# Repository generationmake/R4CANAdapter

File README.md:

# R4CANAdapter
CAN adapter for the Arduino UNO R4 minima and Arduino UNO R4 WiFi

## PCB
### Top

### Bottom

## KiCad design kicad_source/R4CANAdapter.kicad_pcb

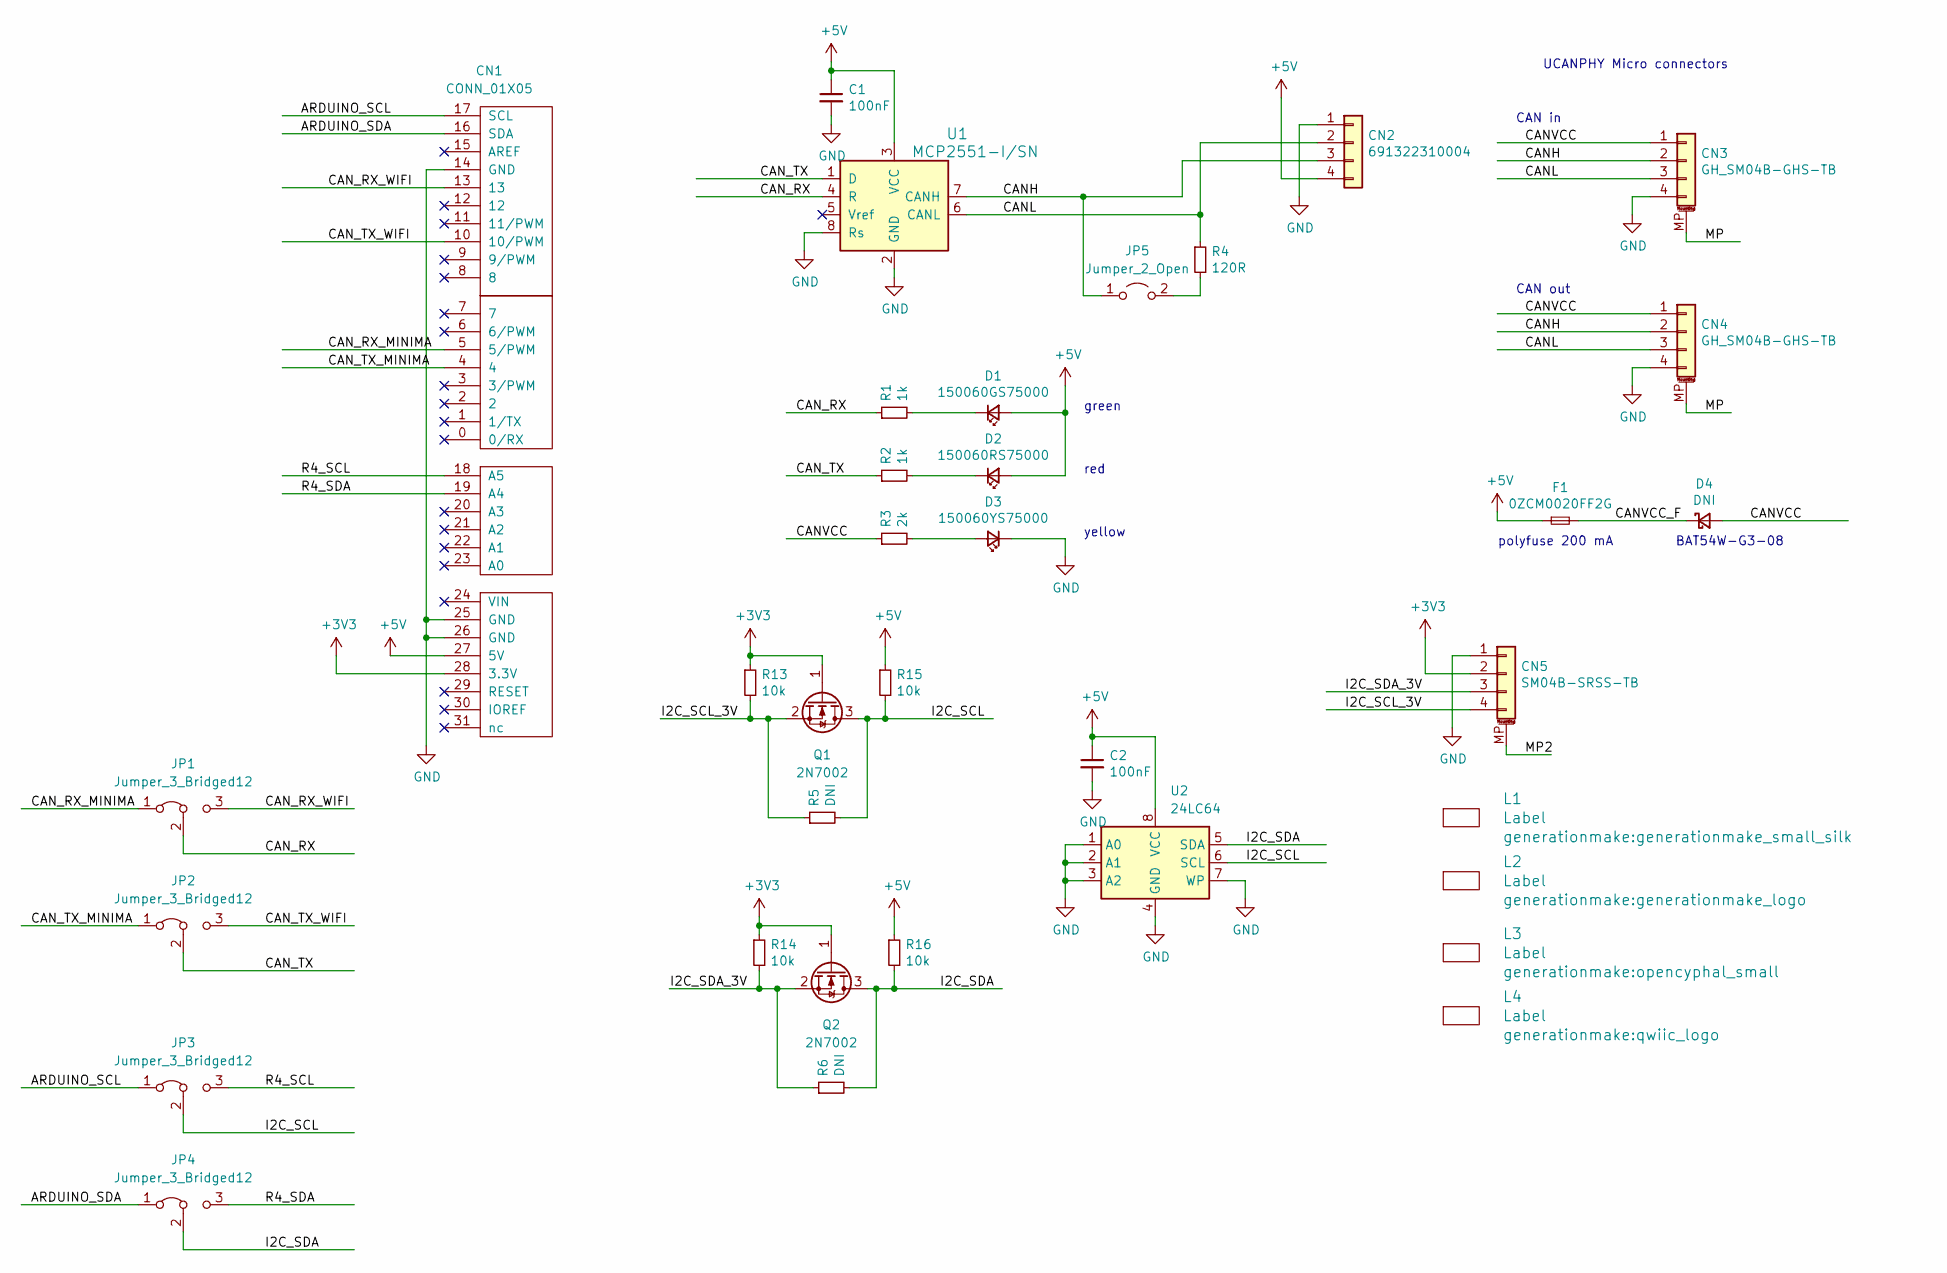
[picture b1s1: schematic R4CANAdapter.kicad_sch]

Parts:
C1, C2: 100nF; C_0603_1608Metric
CN1: CONN_01X05; ARDUINO
CN2: 691322310004; WR-TBL_691322310004
CN3, CN4: GH_SM04B-GHS-TB; JST_GH_SM04B-GHS-TB_1x04-1MP_P1.25mm_Horizontal
CN5: SM04B-SRSS-TB; JST_SH_SM04B-SRSS-TB_1x04-1MP_P1.00mm_Horizontal
D1: 150060GS75000; LED_0603_1608Metric
D2: 150060RS75000; LED_0603_1608Metric
D3: 150060YS75000; LED_0603_1608Metric
D4: DNI; D_SOD-123
F1: 0ZCM0020FF2G; R_0603_1608Metric
JP1, JP2, JP3, JP4: Jumper_3_Bridged12; PinHeader_1x03_P2.54mm_Vertical
JP5: Jumper_2_Open; PinHeader_1x02_P2.54mm_Vertical
L1: Label; generationmake_small_silk
L2: Label; generationmake_logo
L3: Label; opencyphal_small
L4: Label; qwiic_logo
Q1, Q2: 2N7002; SOT-23
R1, R2: 1k; R_0603_1608Metric
R3: 2k; R_0603_1608Metric
R4: 120R; R_0603_1608Metric
R5, R6: DNI; R_0603_1608Metric
R13, R14, R15, R16: 10k; R_0603_1608Metric
U1: MCP2551-I/SN; SOIC-8_3.9x4.9mm_P1.27mm
U2: 24LC64; SOIC-8_3.9x4.9mm_P1.27mm

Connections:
+3V3: CN1.28 (3.3V), CN5.2, Q1.1 (G), Q2.1 (G), R13.1, R14.1
+5V: C1.1, C2.1, CN1.27 (5V), CN2.4, D1.2 (A), D2.2 (A), F1.1, R15.1, R16.1, U1.3 (VCC), U2.8 (VCC)
/ARDUINO_SCL: CN1.17 (SCL), JP3.1 (A)
/ARDUINO_SDA: CN1.16 (SDA), JP4.1 (A)
/CANH: CN2.3, CN3.2, CN4.2, JP5.1 (A), U1.7 (CANH)
/CANL: CN2.2, CN3.3, CN4.3, R4.1, U1.6 (CANL)
/CANVCC: CN3.1, CN4.1, D4.2 (A), R3.1
/CANVCC_F: D4.1 (K), F1.2
/CAN_RX: JP1.2 (C), R1.1, U1.4 (R)
/CAN_RX_MINIMA: CN1.5 (5/PWM), JP1.1 (A)
/CAN_RX_WIFI: CN1.13, JP1.3 (B)
/CAN_TX: JP2.2 (C), R2.1, U1.1 (D)
/CAN_TX_MINIMA: CN1.4, JP2.1 (A)
/CAN_TX_WIFI: CN1.10 (10/PWM), JP2.3 (B)
/I2C_SCL: JP3.2 (C), Q1.3 (D), R5.2, R15.2, U2.6 (SCL)
/I2C_SCL_3V: CN5.4, Q1.2 (S), R5.1, R13.2
/I2C_SDA: JP4.2 (C), Q2.3 (D), R6.2, R16.2, U2.5 (SDA)
/I2C_SDA_3V: CN5.3, Q2.2 (S), R6.1, R14.2
/MP: CN3.MP (MountPin), CN4.MP (MountPin)
/MP2: CN5.MP (MountPin)
/R4_SCL: CN1.18 (A5), JP3.3 (B)
/R4_SDA: CN1.19 (A4), JP4.3 (B)
GND: C1.2, C2.2, CN1.14 (GND), CN1.25 (GND), CN1.26 (GND), CN2.1, CN3.4, CN4.4, CN5.1, D3.1 (K), U1.2 (GND), U1.8 (Rs), U2.1 (A0), U2.2 (A1), U2.3 (A2), U2.4 (GND), U2.7 (WP)
unnamed: D1.1 (K), R1.2
unnamed: D2.1 (K), R2.2
unnamed: D3.2 (A), R3.2
unnamed: JP5.2 (B), R4.2

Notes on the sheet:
CAN out
polyfuse 200 mA
CAN in
yellow
red
UCANPHY Micro connectors
BAT54W-G3-08
green

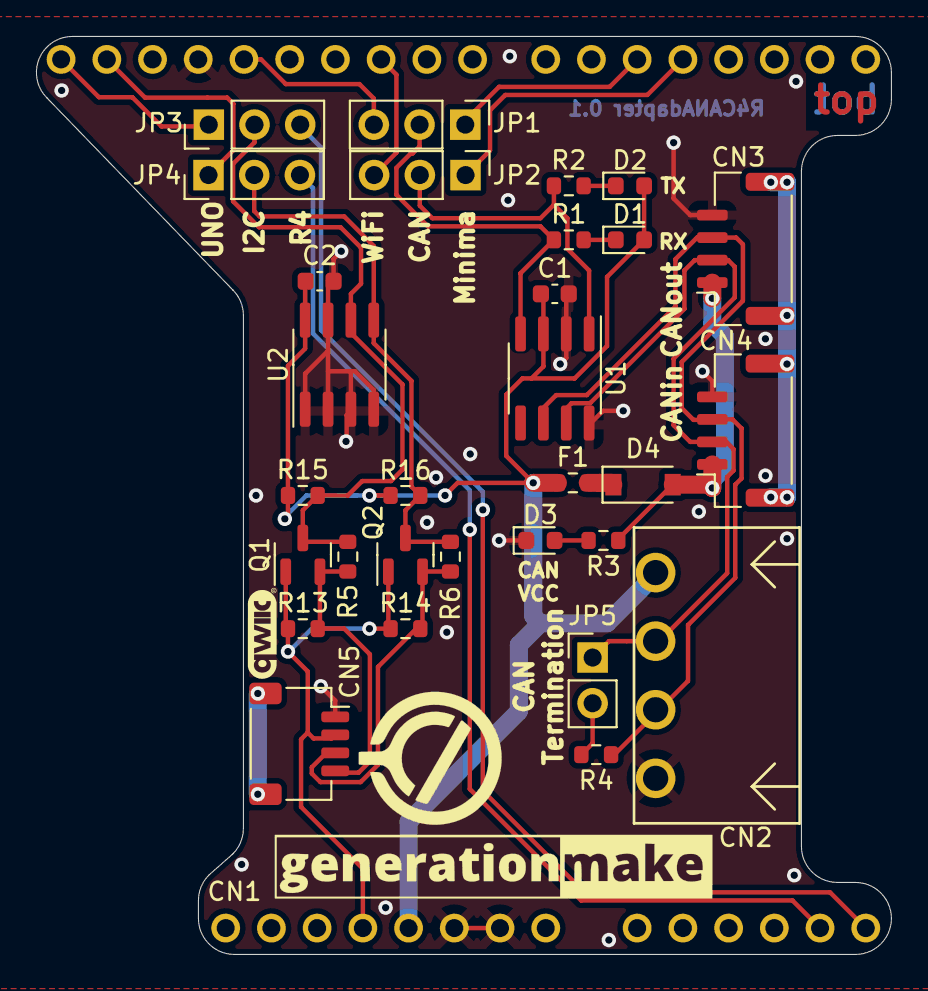
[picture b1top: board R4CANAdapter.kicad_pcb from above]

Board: 2 copper layers, 47.5 x 51.0 mm, 35 parts (1 on the bottom side), 26 nets.

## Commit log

2023-08-12 added kicad project
2023-08-12 added Arduino Uno connector
2023-08-13 added I2C and eeprom
2023-08-14 beautified layout
2023-08-14 added rendering
2023-08-14 added pdf schematic
2023-08-16 used real jumpers
2023-08-16 switched I2C eeprom and CAN driver to the 5V domain
2023-08-16 added bypass resistors for I2C circuit
2023-08-16 updated schematic pdf and image
2023-08-18 added jumper for CAN termination
2023-08-18 added some labels, beautified layout, made DRC
2023-08-18 updated schematic pdf
2023-08-18 updated images
2023-08-18 added license
